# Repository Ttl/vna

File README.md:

Homemade 30 MHZ - 6 GHz single receiver VNA design files.

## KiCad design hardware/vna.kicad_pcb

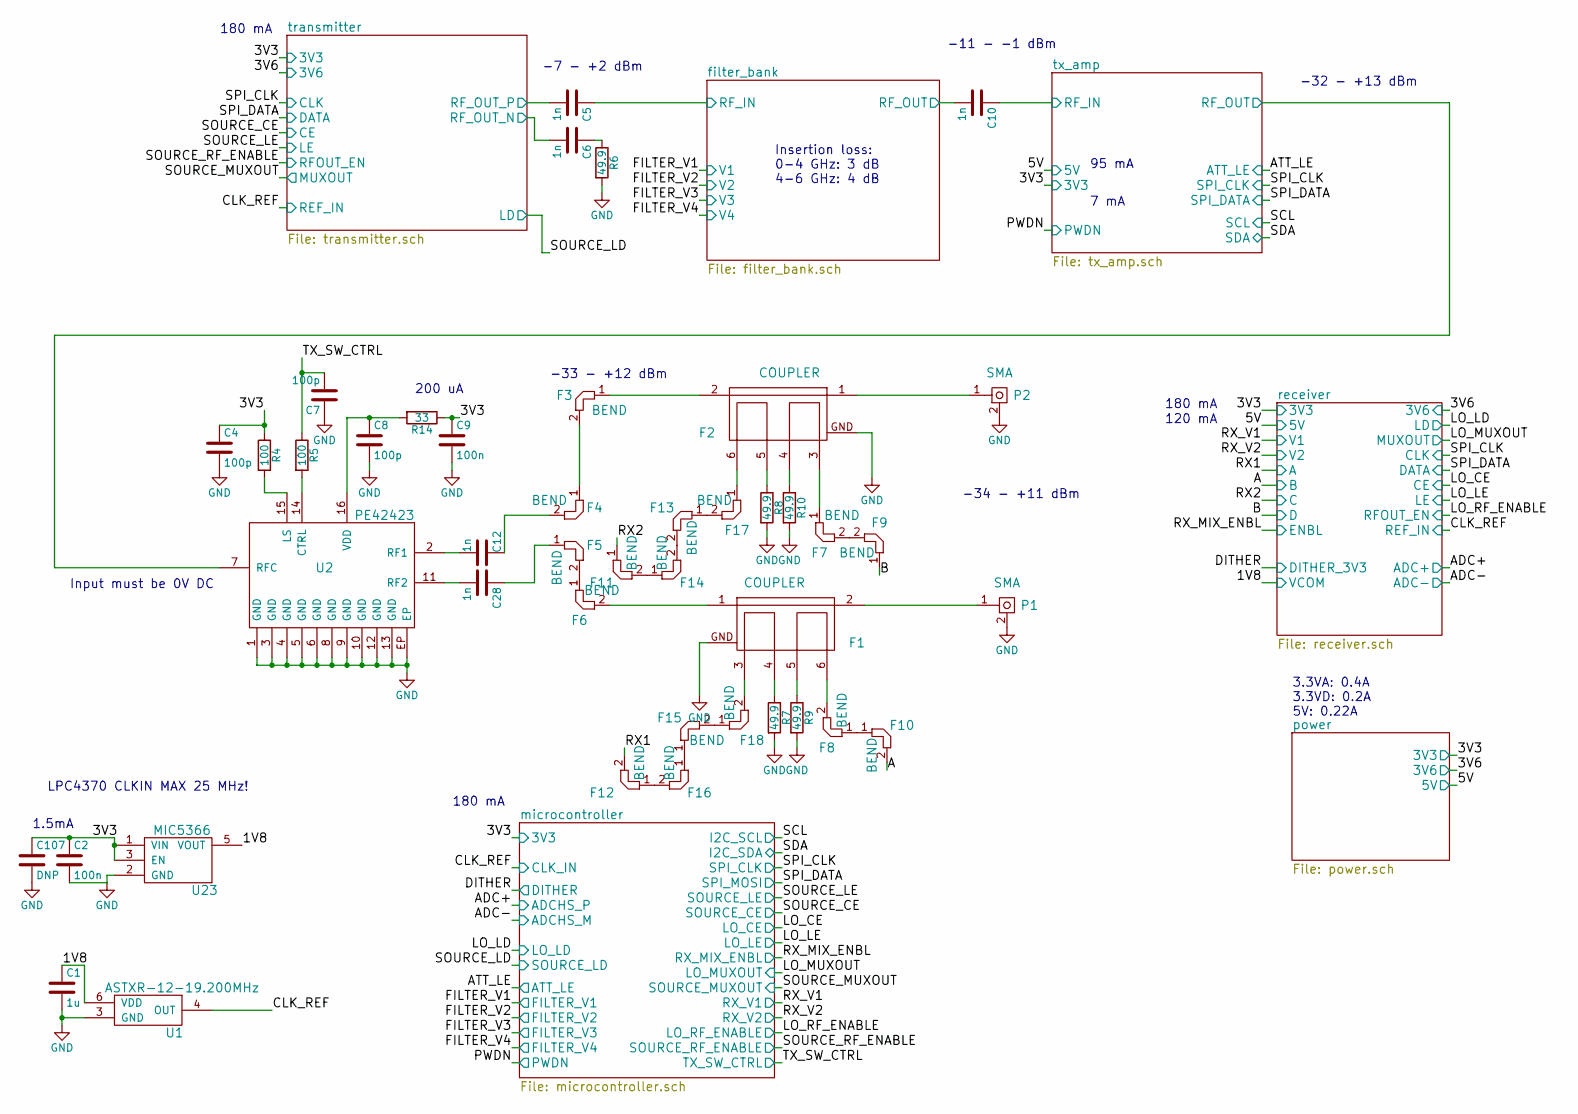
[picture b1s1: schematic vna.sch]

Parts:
C1: 1u; C_0402b
C2, C9: 100n; C_0402b
C4, C7, C8: 100p; C_0402b
C5, C6, C10, C12, C28: 1n; C_0402b
C107: DNP; C_0805b
F1, F2: COUPLER; coupler4
F3, F4, F5, F6, F7, F8, F9, F10, F11, F12, F13, F14, F15, F16, F17, F18: BEND; uwmiter_0.34_0.17_45
P1, P2: SMA; CONSMA003.062
R4, R5: 100; R_0402b
R6, R7, R8, R9, R10: 49.9; R_0402b
R14: 33; R_0402b
U1: ASTXR-12-19.200MHz; ASTRX-12
U2: PE42423; VQFN-16
U23: MIC5366; SOT-353

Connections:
/filter_bank/RF_IN: C5.1; also elsewhere on the board
/filter_bank/RF_OUT: C10.2; also elsewhere on the board
/microcontroller/3V3: C2.1, C4.1, C9.1, C107.1, R4.1, R14.1, U23.1 (VIN), U23.3 (EN); also elsewhere on the board
/microcontroller/CLK_IN: U1.4 (OUT); also elsewhere on the board
/microcontroller/TX_SW_CTRL: C7.2, R5.1; also elsewhere on the board
/receiver/A: F12.2; also elsewhere on the board
/receiver/B: F10.2; also elsewhere on the board
/receiver/C: F11.1; also elsewhere on the board
/receiver/D: F9.1; also elsewhere on the board
/receiver/VCOM: C1.1, U1.6 (VDD), U23.5 (VOUT); also elsewhere on the board
/transmitter/RF_OUT_N: C6.2; also elsewhere on the board
/transmitter/RF_OUT_P: C5.2; also elsewhere on the board
/tx_amp/RF_IN: C10.1; also elsewhere on the board
/tx_amp/RF_OUT: U2.7 (RFC); also elsewhere on the board
GND: C1.2, C2.2, C4.2, C7.1, C8.2, C9.2, C107.2, F1.GND, F2.GND, P1.2, P2.2, R6.2, R7.2, R8.2, R9.2, R10.2, U1.3 (GND), U2.1 (GND), U2.3 (GND), U2.4 (GND), U2.5 (GND), U2.6 (GND), U2.8 (GND), U2.9 (GND), U2.10 (GND), U2.12 (GND), U2.13 (GND), U2.EP, U23.2 (GND); also elsewhere on the board
unnamed: C6.1, R6.1
unnamed: C8.1, R14.2, U2.16 (VDD)
unnamed: C12.1, F4.2
unnamed: C12.2, U2.2 (RF1)
unnamed: C28.1, F5.1
unnamed: C28.2, U2.11 (RF2)
unnamed: F1.1, F6.2
unnamed: F1.2, P1.1
unnamed: F1.3, F18.2
unnamed: F1.4, R7.1
unnamed: F1.5, R9.1
unnamed: F1.6, F8.2
unnamed: F2.1, P2.1
unnamed: F2.2, F3.1
unnamed: F2.3, F7.1
unnamed: F2.4, R10.1
unnamed: F2.5, R8.1
unnamed: F3.2, F4.1
unnamed: F5.2, F6.1
unnamed: F7.2, F9.2
unnamed: F8.1, F10.1
unnamed: F11.2, F14.1
unnamed: F12.1, F16.2
unnamed: F13.1, F17.2
unnamed: F13.2, F14.2
unnamed: F15.1, F16.1
unnamed: F15.2, F18.1
unnamed: F2.6, F17.1
unnamed: R4.2, U2.15 (LS)
unnamed: R5.2, U2.14 (CTRL)

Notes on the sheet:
1.5mA
Input must be 0V DC
Insertion loss: 0-4 GHz: 3 dB 4-6 GHz: 4 dB
-7 - +2 dBm
-11 - -1 dBm
-32 - +13 dBm
-33 - +12 dBm
-34 - +11 dBm
200 uA
180 mA
120 mA
3.3VA: 0.4A 3.3VD: 0.2A 5V: 0.22A
LPC4370 CLKIN MAX 25 MHz!
95 mA
7 mA

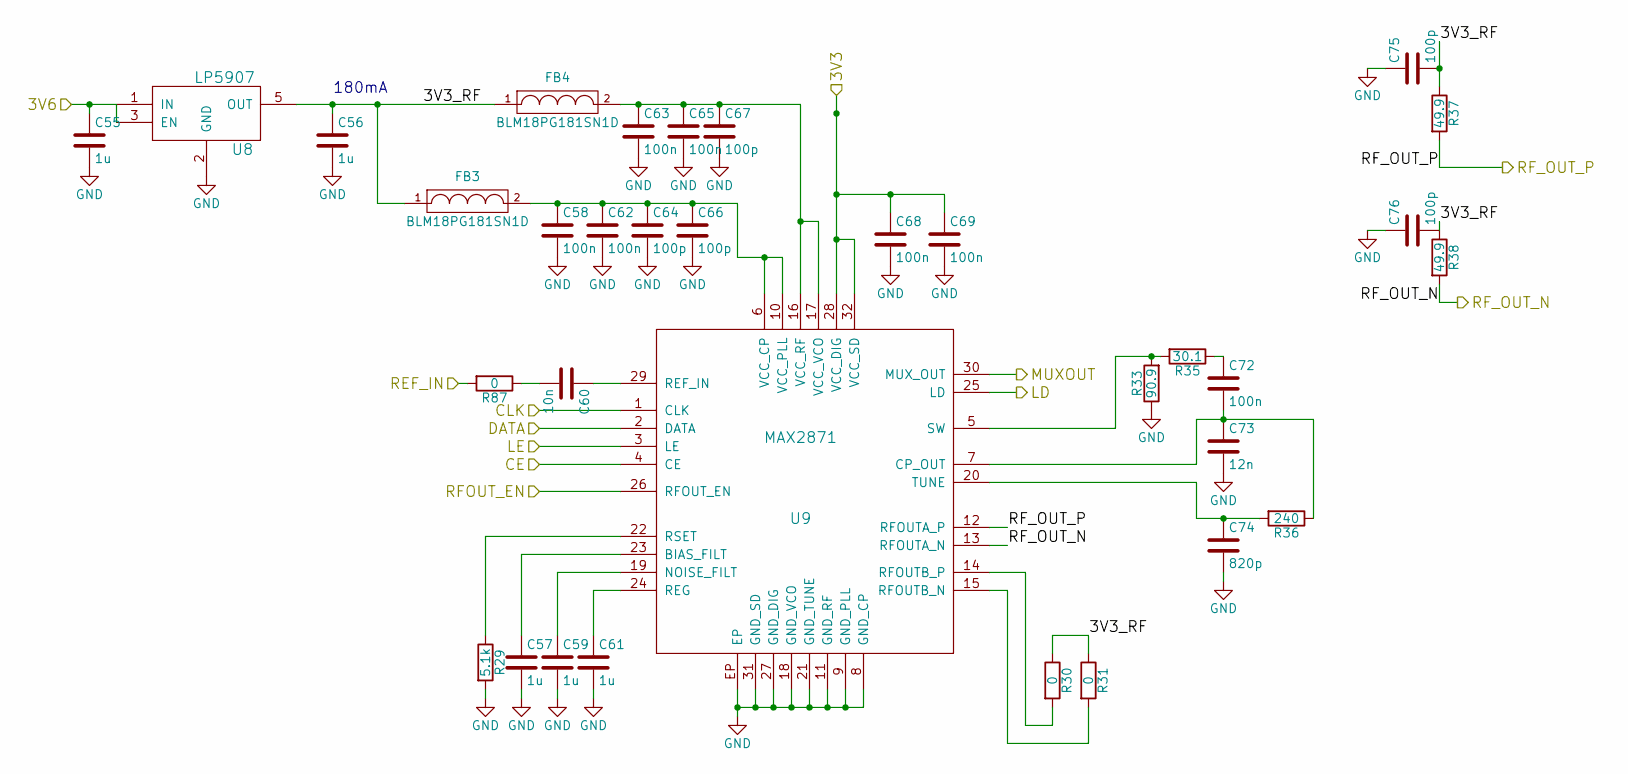
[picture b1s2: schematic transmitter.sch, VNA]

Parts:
C13, C14, C15, C17, C19: 1u; C_0603b
C16, C20, C21, C23, C26, C27, C30: 100n; C_0402b
C18: 10n; C_0402b
C22, C24, C25, C33, C34: 100p; C_0402b
C31: 12n; C_0402b
C32: 820p; C_0402b
FB1, FB2: BLM18PG181SN1D; C_0603b
R11: 5.1k; R_0402b
R12, R13, R86: 0; R_0402b
R15: 90.9; R_0402b
R17: 30.1; R_0402b
R18: 240; R_0402b
R19, R20: 49.9; R_0402b
U4: LP5907; SOT-23-5
U5: MAX2871; TQFN-32

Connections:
/microcontroller/3V3: C26.1, C27.1, U5.28 (VCC_DIG), U5.32 (VCC_SD); also elsewhere on the board
/microcontroller/CLK_IN: R86.2; also elsewhere on the board
/power/3V6: C13.1, U4.1 (IN), U4.3 (EN); also elsewhere on the board
/receiver/CLK: U5.1 (CLK); also elsewhere on the board
/receiver/DATA: U5.2 (DATA); also elsewhere on the board
/transmitter/3V3_RF: C14.1, C33.2, C34.2, FB1.1, FB2.1, R12.1, R13.1, R19.1, R20.1, U4.5 (OUT)
/transmitter/CE: U5.4 (CE); also elsewhere on the board
/transmitter/LD: U5.25 (LD); also elsewhere on the board
/transmitter/LE: U5.3 (LE); also elsewhere on the board
/transmitter/MUXOUT: U5.30 (MUX_OUT); also elsewhere on the board
/transmitter/RFOUT_EN: U5.26 (RFOUT_EN); also elsewhere on the board
/transmitter/RF_OUT_N: R20.2, U5.13 (RFOUTA_N); also elsewhere on the board
/transmitter/RF_OUT_P: R19.2, U5.12 (RFOUTA_P); also elsewhere on the board
GND: C13.2, C14.2, C15.2, C16.2, C17.2, C19.2, C20.2, C21.2, C22.2, C23.2, C24.2, C25.2, C26.2, C27.2, C31.2, C32.2, C33.1, C34.1, R11.2, R15.1, U4.2 (GND), U5.8 (GND_CP), U5.9 (GND_PLL), U5.11 (GND_RF), U5.18 (GND_VCO), U5.21 (GND_TUNE), U5.27 (GND_DIG), U5.31 (GND_SD), U5.EP; also elsewhere on the board
unnamed: C15.1, U5.23 (BIAS_FILT)
unnamed: C16.1, C20.1, C22.1, C24.1, FB1.2, U5.6 (VCC_CP), U5.10 (VCC_PLL)
unnamed: C17.1, U5.19 (NOISE_FILT)
unnamed: C18.1, U5.29 (REF_IN)
unnamed: C18.2, R86.1
unnamed: C19.1, U5.24 (REG)
unnamed: C21.1, C23.1, C25.1, FB2.2, U5.16 (VCC_RF), U5.17 (VCC_VCO)
unnamed: C30.1, R17.1
unnamed: C30.2, C31.1, R18.1, U5.7 (CP_OUT)
unnamed: C32.1, R18.2, U5.20 (TUNE)
unnamed: R11.1, U5.22 (RSET)
unnamed: R12.2, U5.14 (RFOUTB_P)
unnamed: R13.2, U5.15 (RFOUTB_N)
unnamed: R15.2, R17.2, U5.5 (SW)

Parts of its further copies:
C55, C56, C57, C59, C61: 1u; C_0603b
C58, C62, C63, C65, C68, C69, C72: 100n; C_0402b
C60: 10n; C_0402b
C64, C66, C67, C75, C76: 100p; C_0402b
C73: 12n; C_0402b
C74: 820p; C_0402b
FB3, FB4: BLM18PG181SN1D; C_0603b
R29: 5.1k; R_0402b
R30, R31, R87: 0; R_0402b
R33: 90.9; R_0402b
R35: 30.1; R_0402b
R36: 240; R_0402b
R37, R38: 49.9; R_0402b
U8: LP5907; SOT-23-5
U9: MAX2871; TQFN-32

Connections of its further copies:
/microcontroller/3V3: C68.1, C69.1, U9.28 (VCC_DIG), U9.32 (VCC_SD); also elsewhere on the board
/microcontroller/CLK_IN: R87.2; also elsewhere on the board
/microcontroller/LO_MUXOUT: U9.30 (MUX_OUT); also elsewhere on the board
/microcontroller/LO_RF_ENABLE: U9.26 (RFOUT_EN); also elsewhere on the board
/power/3V6: C55.1, U8.1 (IN), U8.3 (EN); also elsewhere on the board
/receiver/CE: U9.4 (CE); also elsewhere on the board
/receiver/CLK: U9.1 (CLK); also elsewhere on the board
/receiver/DATA: U9.2 (DATA); also elsewhere on the board
/receiver/LD: U9.25 (LD); also elsewhere on the board
/receiver/LE: U9.3 (LE); also elsewhere on the board
/receiver/lo_synth/3V3_RF: C56.1, C75.2, C76.2, FB3.1, FB4.1, R30.1, R31.1, R37.1, R38.1, U8.5 (OUT)
/receiver/lo_synth/RF_OUT_N: R38.2, U9.13 (RFOUTA_N); also elsewhere on the board
/receiver/lo_synth/RF_OUT_P: R37.2, U9.12 (RFOUTA_P); also elsewhere on the board
GND: C55.2, C56.2, C57.2, C58.2, C59.2, C61.2, C62.2, C63.2, C64.2, C65.2, C66.2, C67.2, C68.2, C69.2, C73.2, C74.2, C75.1, C76.1, R29.2, R33.1, U8.2 (GND), U9.8 (GND_CP), U9.9 (GND_PLL), U9.11 (GND_RF), U9.18 (GND_VCO), U9.21 (GND_TUNE), U9.27 (GND_DIG), U9.31 (GND_SD), U9.EP; also elsewhere on the board
unnamed: C57.1, U9.23 (BIAS_FILT)
unnamed: C58.1, C62.1, C64.1, C66.1, FB3.2, U9.6 (VCC_CP), U9.10 (VCC_PLL)
unnamed: C59.1, U9.19 (NOISE_FILT)
unnamed: C60.1, U9.29 (REF_IN)
unnamed: C60.2, R87.1
unnamed: C61.1, U9.24 (REG)
unnamed: C63.1, C65.1, C67.1, FB4.2, U9.16 (VCC_RF), U9.17 (VCC_VCO)
unnamed: C72.1, R35.1
unnamed: C72.2, C73.1, R36.1, U9.7 (CP_OUT)
unnamed: C74.1, R36.2, U9.20 (TUNE)
unnamed: R29.1, U9.22 (RSET)
unnamed: R30.2, U9.14 (RFOUTB_P)
unnamed: R31.2, U9.15 (RFOUTB_N)
unnamed: R33.2, R35.2, U9.5 (SW)

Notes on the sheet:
180mA

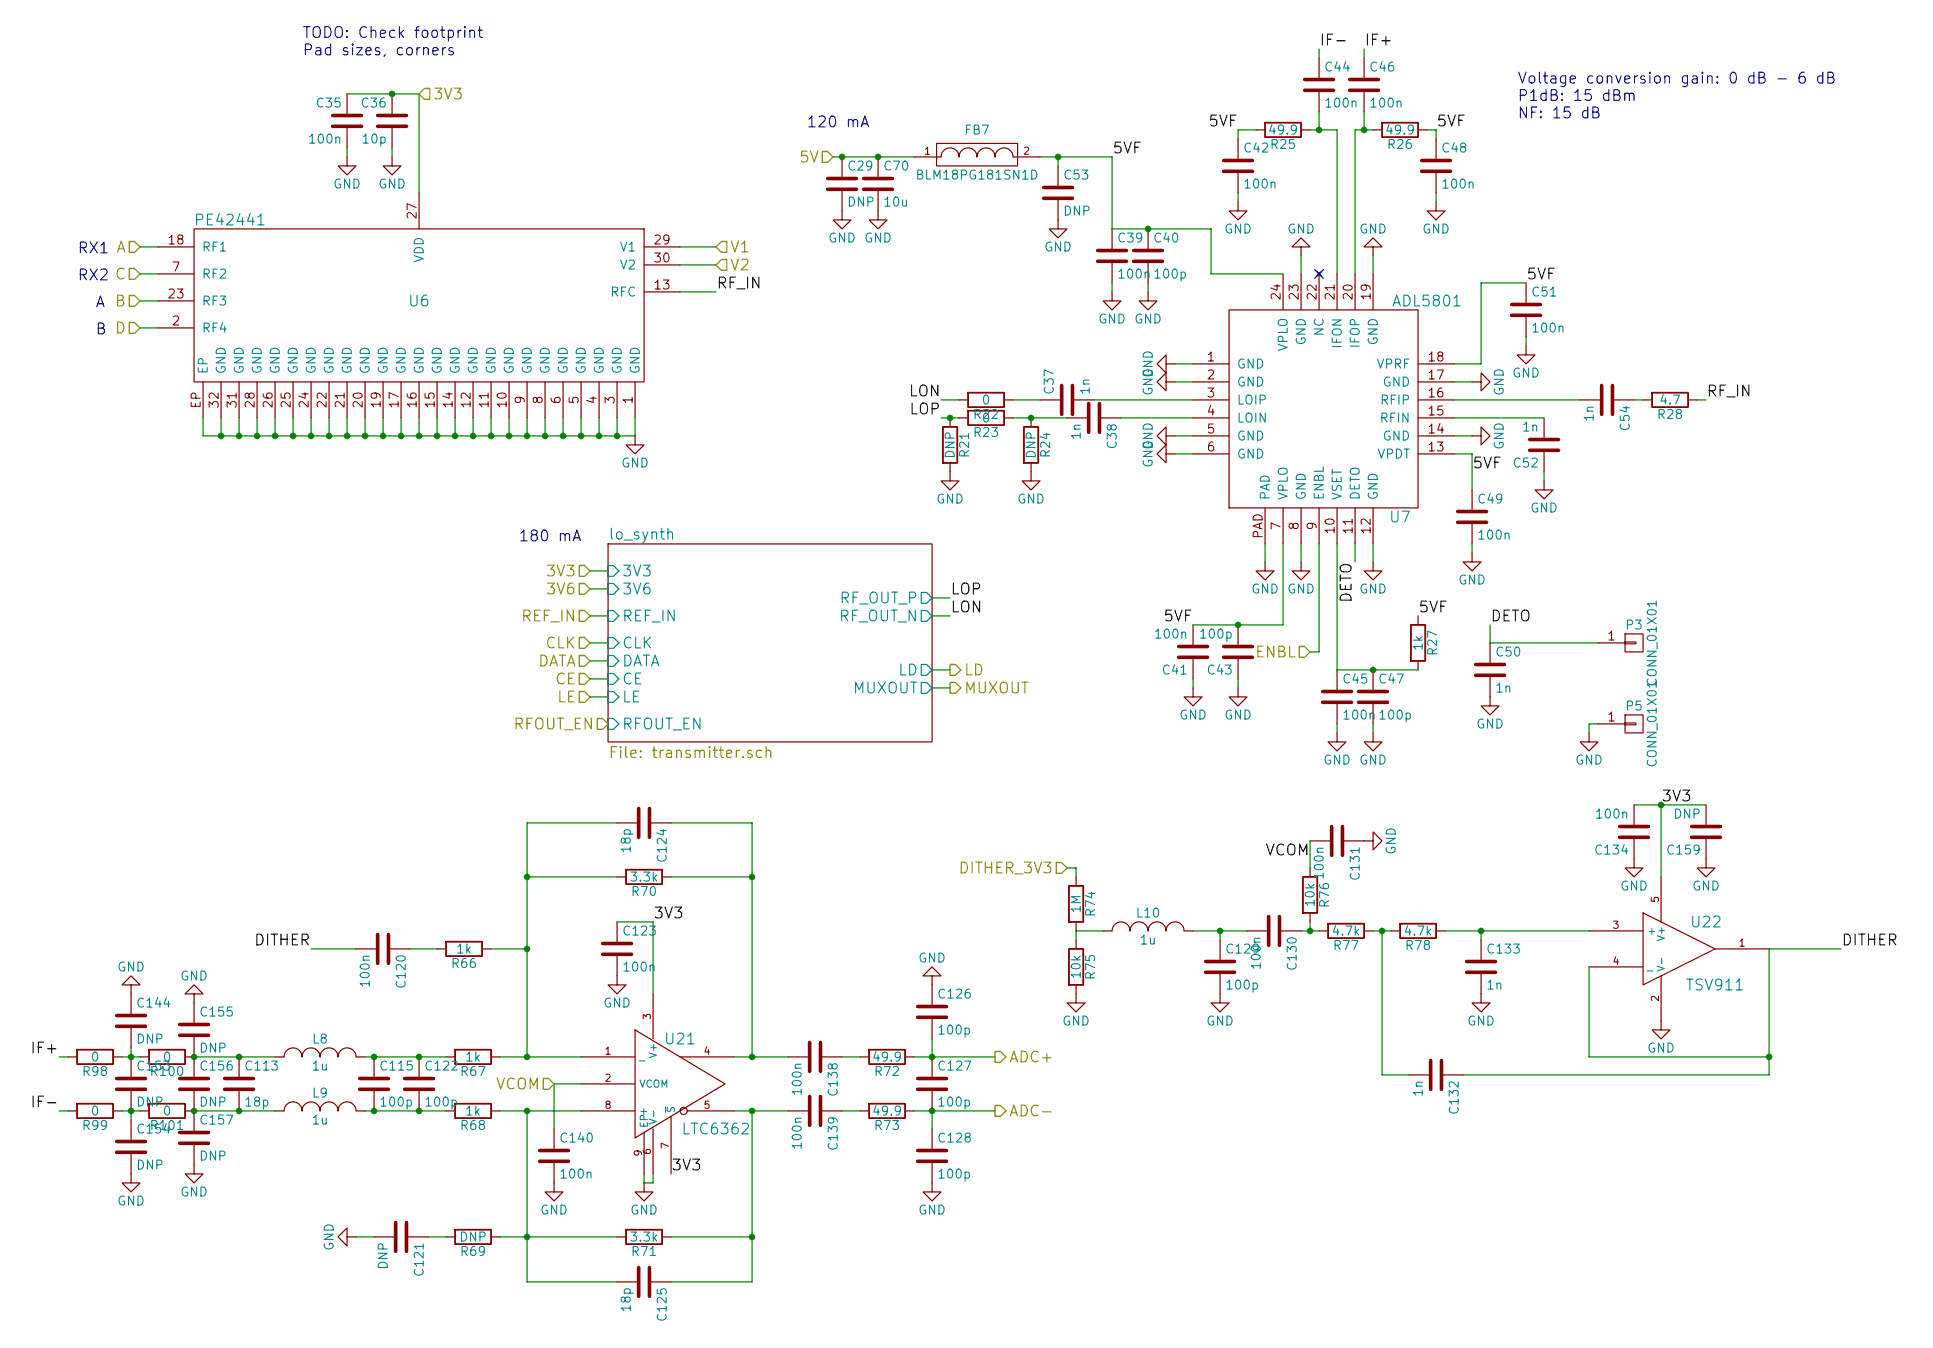
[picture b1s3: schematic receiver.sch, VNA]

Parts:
C29: DNP; C_0603b
C35, C39, C41, C42, C44, C45, C46, C48, C49, C51, C120, C123, C130, C131, C134, C138, C139, C140: 100n; C_0402b
C36: 10p; C_0402b
C37, C38, C50, C52, C54, C132, C133: 1n; C_0402b
C40, C43, C47, C115, C122, C126, C127, C128, C129: 100p; C_0402b
C53, C159: DNP; C_0805b
C70: 10u; C_0805b
C113, C124, C125: 18p; C_0402b
C121, C144, C153, C154, C155, C156, C157: DNP; C_0402b
FB7: BLM18PG181SN1D; C_0603b
L8, L9, L10: 1u; C_0603b
P3, P5: CONN_01X01; TP_1.00
R21, R24, R69: DNP; R_0402b
R22, R23, R98, R99, R100, R101: 0; R_0402b
R25, R26, R72, R73: 49.9; R_0402b
R27, R66, R67, R68: 1k; R_0402b
R28: 4.7; R_0402b
R70, R71: 3.3k; R_0402b
R74: 1M; R_0402b
R75, R76: 10k; R_0402b
R77, R78: 4.7k; R_0402b
U6: PE42441; VFQFN-32
U7: ADL5801; VFQFN-24
U21: LTC6362; DFN-8-1EP_3x3mm_Pitch0.5mm
U22: TSV911; SOT-23-5

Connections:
/microcontroller/3V3: C35.1, C36.1, C123.1, C134.2, C159.2, U6.27 (VDD), U21.3 (V+), U21.7 (~S), U22.5 (V+); also elsewhere on the board
/microcontroller/DITHER: R74.1; also elsewhere on the board
/microcontroller/RX_V1: U6.29 (V1); also elsewhere on the board
/microcontroller/RX_V2: U6.30 (V2); also elsewhere on the board
/power/5V: C29.1, C70.1, FB7.1; also elsewhere on the board
/receiver/5VF: C39.1, C40.1, C41.2, C42.1, C43.2, C48.1, C49.1, C51.1, C53.1, FB7.2, R25.2, R26.1, R27.1, U7.7 (VPLO), U7.13 (VPDT), U7.18 (VPRF), U7.24 (VPLO)
/receiver/A: U6.18 (RF1); also elsewhere on the board
/receiver/ADC+: C126.2, C127.1, R72.1; also elsewhere on the board
/receiver/ADC-: C127.2, C128.1, R73.1; also elsewhere on the board
/receiver/B: U6.23 (RF3); also elsewhere on the board
/receiver/C: U6.7 (RF2); also elsewhere on the board
/receiver/D: U6.2 (RF4); also elsewhere on the board
/receiver/DETO: C50.1, P3.1, U7.11 (DETO)
/receiver/DITHER: C120.2, C132.1, U22.1, U22.4 (_)
/receiver/ENBL: U7.9 (ENBL); also elsewhere on the board
/receiver/IF+: C46.1, R98.2
/receiver/IF-: C44.1, R99.2
/receiver/RF_IN: R28.1, U6.13 (RFC)
/receiver/VCOM: C131.2, C140.1, R76.1, U21.2 (VCOM); also elsewhere on the board
/receiver/lo_synth/RF_OUT_N: R22.2; also elsewhere on the board
/receiver/lo_synth/RF_OUT_P: R21.1, R23.2; also elsewhere on the board
GND: C29.2, C35.2, C36.2, C39.2, C40.2, C41.1, C42.2, C43.1, C45.2, C47.2, C48.2, C49.2, C50.2, C51.2, C52.1, C53.2, C70.2, C121.2, C123.2, C126.1, C128.2, C129.2, C131.1, C133.2, C134.1, C140.2, C144.1, C154.2, C155.1, C157.2, C159.1, P5.1, R21.2, R24.2, R75.2, U6.1 (GND), U6.3 (GND), U6.4 (GND), U6.5 (GND), U6.6 (GND), U6.8 (GND), U6.9 (GND), U6.10 (GND), U6.11 (GND), U6.12 (GND), U6.14 (GND), U6.15 (GND), U6.16 (GND), U6.17 (GND), U6.19 (GND), U6.20 (GND), U6.21 (GND), U6.22 (GND), U6.24 (GND), U6.25 (GND), U6.26 (GND), U6.28 (GND), U6.31 (GND), U6.32 (GND), U6.EP, U7.1 (GND), U7.2 (GND), U7.5 (GND), U7.6 (GND), U7.8 (GND), U7.12 (GND), U7.14 (GND), U7.17 (GND), U7.19 (GND), U7.23 (GND), U7.PAD, U21.6 (V-), U21.9 (EP), U22.2 (V-); also elsewhere on the board
unnamed: C37.1, R22.1
unnamed: C37.2, U7.3 (LOIP)
unnamed: C38.1, U7.4 (LOIN)
unnamed: C38.2, R23.1, R24.1
unnamed: C44.2, R25.1, U7.21 (IFON)
unnamed: C45.1, C47.1, R27.2, U7.10 (VSET)
unnamed: C46.2, R26.2, U7.20 (IFOP)
unnamed: C52.2, U7.15 (RFIN)
unnamed: C54.1, R28.2
unnamed: C54.2, U7.16 (RFIP)
unnamed: C113.1, C155.2, C156.1, L8.1, R100.1
unnamed: C113.2, C156.2, C157.1, L9.1, R101.1
unnamed: C115.1, C122.1, L8.2, R67.2
unnamed: C115.2, C122.2, L9.2, R68.2
unnamed: C120.1, R66.2
unnamed: C121.1, R69.2
unnamed: C124.1, C138.2, R70.1, U21.4
unnamed: C124.2, R66.1, R67.1, R70.2, U21.1 (_)
unnamed: C125.1, C139.2, R71.1, U21.5
unnamed: C125.2, R68.1, R69.1, R71.2, U21.8 (+)
unnamed: C129.1, C130.2, L10.2
unnamed: C130.1, R76.2, R77.2
unnamed: C132.2, R77.1, R78.2
unnamed: C133.1, R78.1, U22.3 (+)
unnamed: C138.1, R72.2
unnamed: C139.1, R73.2
unnamed: C144.2, C153.1, R98.1, R100.2
unnamed: C153.2, C154.1, R99.1, R101.2
unnamed: L10.1, R74.2, R75.1

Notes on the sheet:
TODO: Check footprint Pad sizes, corners
Voltage conversion gain: 0 dB - 6 dB P1dB: 15 dBm NF: 15 dB
120 mA
180 mA
RX1
RX2

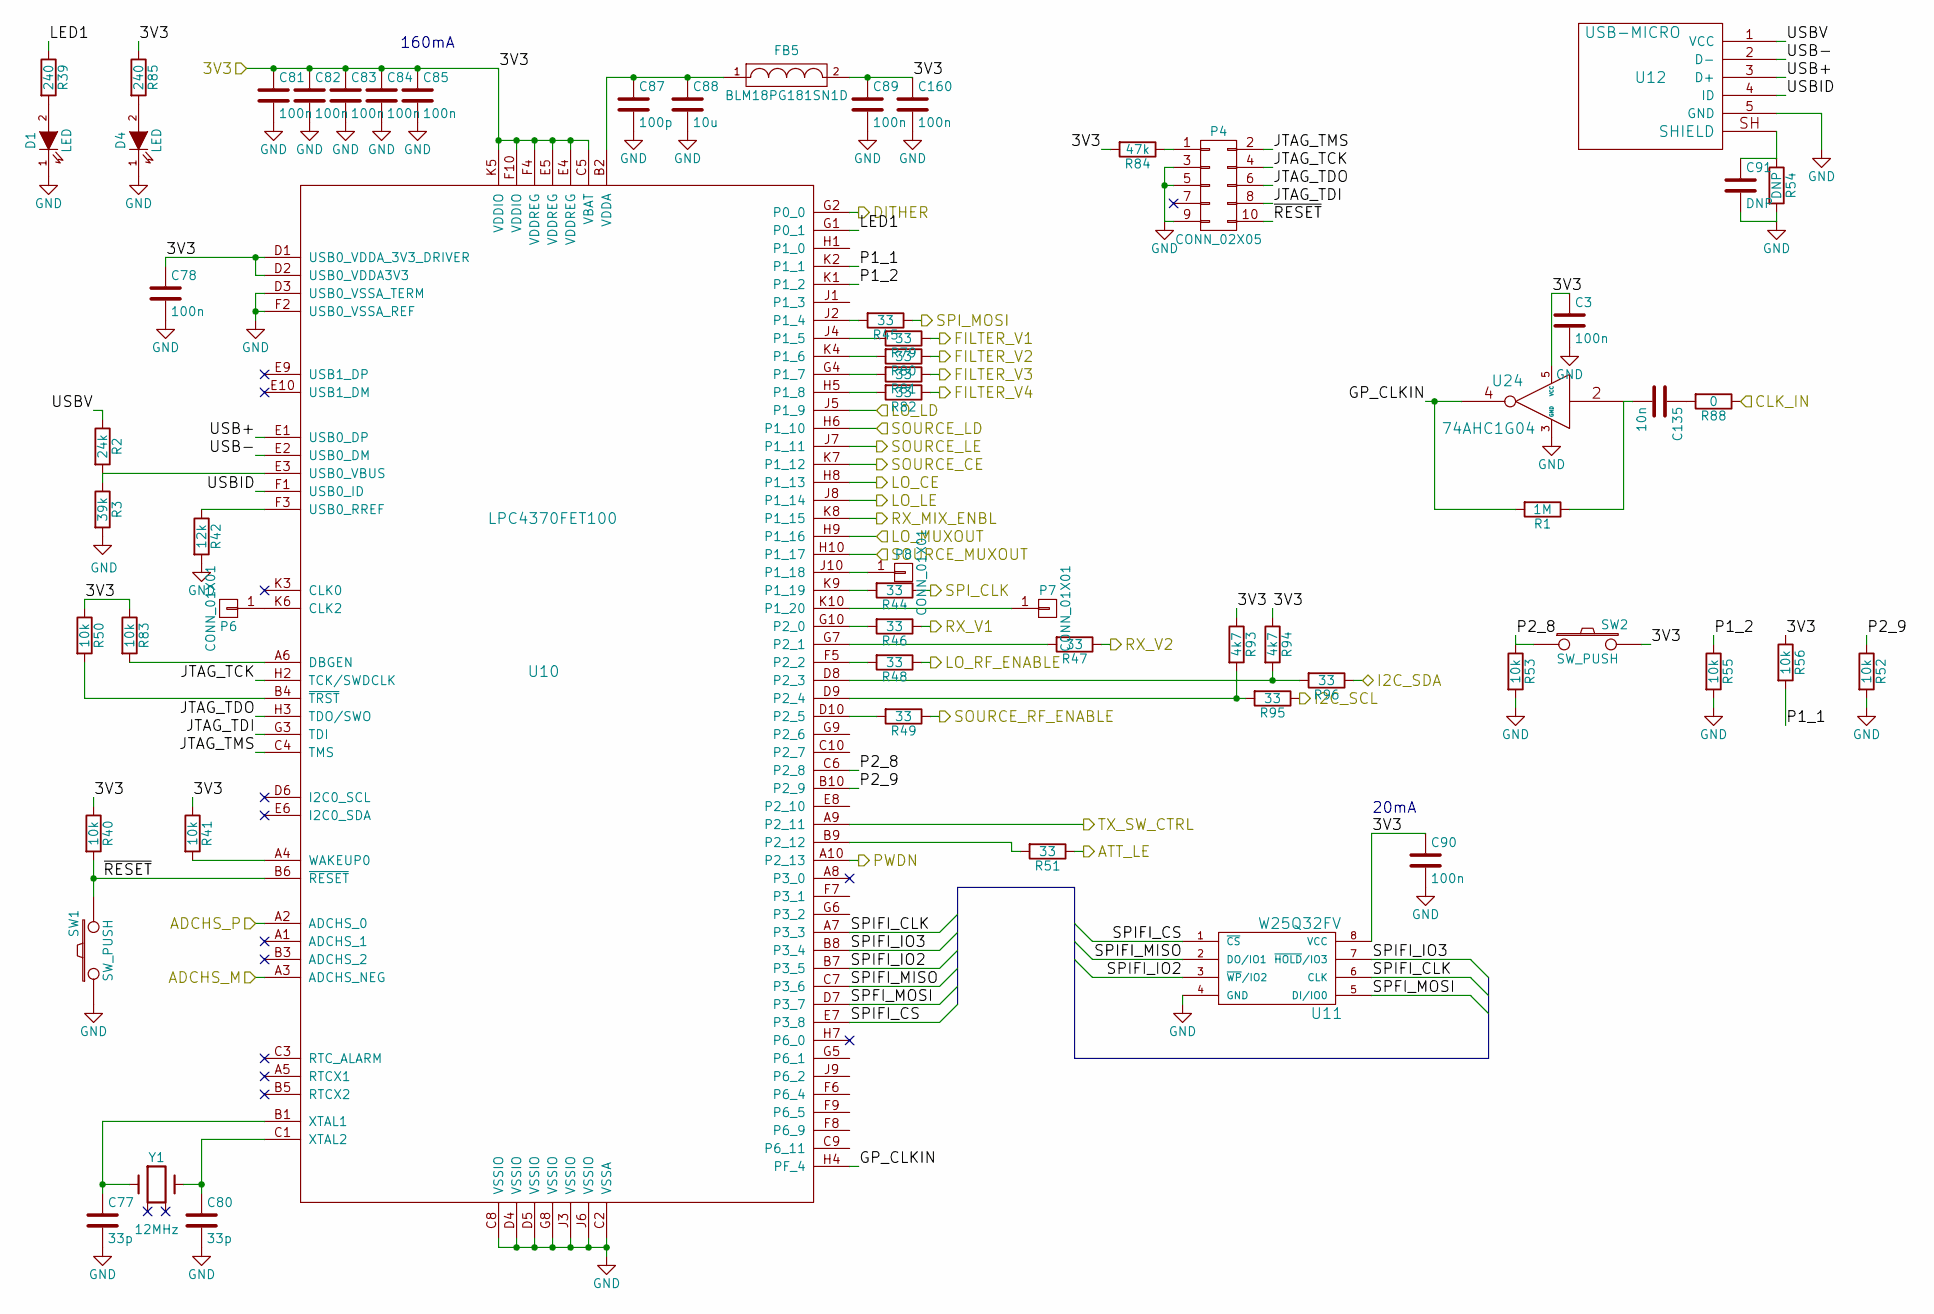
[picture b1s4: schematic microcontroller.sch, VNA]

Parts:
C3, C78, C81, C82, C83, C84, C85, C89, C90, C160: 100n; C_0402b
C77, C80: 33p; C_0402b
C87: 100p; C_0402b
C88: 10u; C_0805b
C91: DNP; C_0402b
C135: 10n; C_0402b
D1, D4: LED; LED_0603
FB5: BLM18PG181SN1D; C_0603b
P4: CONN_02X05; CNC-3220-10-0300-00
P6, P7, P8: CONN_01X01; TP_1.00
R1: 1M; R_0402b
R2: 24k; R_0402b
R3: 39k; R_0402b
R39, R85: 240; R_0402b
R40, R41, R50, R52, R53, R55, R56, R83: 10k; R_0402b
R42: 12k; R_0402b
R44, R45, R46, R47, R48, R49, R51, R79, R80, R81, R82, R95, R96: 33; R_0402b
R54: DNP; R_0402b
R84: 47k; R_0402b
R88: 0; R_0402b
R93, R94: 4k7; R_0402b
SW1, SW2: SW_PUSH; EVP-AWBA2A
U10: LPC4370FET100; TFBGA-100
U11: W25Q32FV; SOIJ-8_5.3x5.3mm_Pitch1.27mm
U12: USB-MICRO; USB_MICRO
U24: 74AHC1G04; SOT-353
Y1: 12MHz; XTAL_3.2x2.5

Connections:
/microcontroller/3V3: C3.1, C78.1, C81.1, C82.1, C83.1, C84.1, C85.1, C89.1, C90.1, C160.1, FB5.2, R40.1, R41.1, R50.1, R56.1, R83.1, R84.2, R85.1, R93.1, R94.1, SW2.2, U10.C5 (VBAT), U10.D1 (USB0_VDDA_3V3_DRIVER), U10.D2 (USB0_VDDA3V3), U10.E4 (VDDREG), U10.E5 (VDDREG), U10.F4 (VDDREG), U10.F10 (VDDIO), U10.K5 (VDDIO), U11.8 (VCC), U24.5 (VCC); also elsewhere on the board
/microcontroller/ATT_LE: R51.1; also elsewhere on the board
/microcontroller/CLK_IN: R88.1; also elsewhere on the board
/microcontroller/DITHER: U10.G2 (P0_0); also elsewhere on the board
/microcontroller/FILTER_V1: R79.1; also elsewhere on the board
/microcontroller/FILTER_V2: R80.1; also elsewhere on the board
/microcontroller/FILTER_V3: R81.1; also elsewhere on the board
/microcontroller/FILTER_V4: R82.1; also elsewhere on the board
/microcontroller/GP_CLKIN: R1.2, U10.H4 (PF_4), U24.4
/microcontroller/I2C_SCL: R95.1; also elsewhere on the board
/microcontroller/I2C_SDA: R96.1; also elsewhere on the board
/microcontroller/JTAG_TCK: P4.4, U10.H2 (TCK/SWDCLK)
/microcontroller/JTAG_TDI: P4.8, U10.G3 (TDI)
/microcontroller/JTAG_TDO: P4.6, U10.H3 (TDO/SWO)
/microcontroller/JTAG_TMS: P4.2, U10.C4 (TMS)
/microcontroller/LED1: R39.1, U10.G1 (P0_1)
/microcontroller/LO_MUXOUT: U10.H9 (P1_16); also elsewhere on the board
/microcontroller/LO_RF_ENABLE: R48.1; also elsewhere on the board
/microcontroller/P1_1: R56.2, U10.K2 (P1_1)
/microcontroller/P1_2: R55.1, U10.K1 (P1_2)
/microcontroller/P2_8: R53.1, SW2.1, U10.C6 (P2_8)
/microcontroller/P2_9: R52.1, U10.B10 (P2_9)
/microcontroller/PWDN: U10.A10 (P2_13); also elsewhere on the board
/microcontroller/RX_V1: R46.1; also elsewhere on the board
/microcontroller/RX_V2: R47.1; also elsewhere on the board
/microcontroller/SPFI_MOSI: U10.D7 (P3_7), U11.5 (DI/IO0)
/microcontroller/SPIFI_CLK: U10.A7 (P3_3), U11.6 (CLK)
/microcontroller/SPIFI_CS: U10.E7 (P3_8), U11.1 (~CS)
/microcontroller/SPIFI_IO2: U10.B7 (P3_5), U11.3 (~WP~/IO2)
/microcontroller/SPIFI_IO3: U10.B8 (P3_4), U11.7 (~HOLD~/IO3)
/microcontroller/SPIFI_MISO: U10.C7 (P3_6), U11.2 (DO/IO1)
/microcontroller/TX_SW_CTRL: U10.A9 (P2_11); also elsewhere on the board
/microcontroller/USB+: U10.E1 (USB0_DP), U12.3 (D+)
/microcontroller/USB-: U10.E2 (USB0_DM), U12.2 (D-)
/microcontroller/USBID: U10.F1 (USB0_ID), U12.4 (ID)
/microcontroller/USBV: R2.1, U12.1 (VCC)
/microcontroller/~RESET: P4.10, R40.2, SW1.2, U10.B6 (~RESET)
/receiver/ADC+: U10.A2 (ADCHS_0); also elsewhere on the board
/receiver/ADC-: U10.A3 (ADCHS_NEG); also elsewhere on the board
/receiver/CE: U10.H8 (P1_13); also elsewhere on the board
/receiver/CLK: R44.1; also elsewhere on the board
/receiver/DATA: R45.1; also elsewhere on the board
/receiver/ENBL: U10.K8 (P1_15); also elsewhere on the board
/receiver/LD: U10.J5 (P1_9); also elsewhere on the board
/receiver/LE: U10.J8 (P1_14); also elsewhere on the board
/transmitter/CE: U10.K7 (P1_12); also elsewhere on the board
/transmitter/LD: U10.H6 (P1_10); also elsewhere on the board
/transmitter/LE: U10.J7 (P1_11); also elsewhere on the board
/transmitter/MUXOUT: U10.H10 (P1_17); also elsewhere on the board
/transmitter/RFOUT_EN: R49.1; also elsewhere on the board
GND: C3.2, C77.2, C78.2, C80.2, C81.2, C82.2, C83.2, C84.2, C85.2, C87.2, C88.2, C89.2, C90.2, C91.2, C160.2, D1.1 (K), D4.1 (K), P4.3, P4.5, P4.9, R3.2, R42.2, R52.2, R53.2, R54.2, R55.2, SW1.1, U10.C2 (VSSA), U10.C8 (VSSIO), U10.D3 (USB0_VSSA_TERM), U10.D4 (VSSIO), U10.D5 (VSSIO), U10.F2 (USB0_VSSA_REF), U10.G8 (VSSIO), U10.J3 (VSSIO), U10.J6 (VSSIO), U11.4 (GND), U12.5 (GND), U24.3 (GND); also elsewhere on the board
unnamed: C77.1, U10.B1 (XTAL1), Y1.1
unnamed: C80.1, U10.C1 (XTAL2), Y1.3
unnamed: C87.1, C88.1, FB5.1, U10.B2 (VDDA)
unnamed: C91.1, R54.1, U12.SH (SHIELD)
unnamed: C135.1, R88.2
unnamed: C135.2, R1.1, U24.2
unnamed: D1.2 (A), R39.2
unnamed: D4.2 (A), R85.2
unnamed: P4.1, R84.1
unnamed: P6.1, U10.K6 (CLK2)
unnamed: P7.1, U10.K10 (P1_20)
unnamed: P8.1, U10.J10 (P1_18)
unnamed: R2.2, R3.1, U10.E3 (USB0_VBUS)
unnamed: R41.2, U10.A4 (WAKEUP0)
unnamed: R42.1, U10.F3 (USB0_RREF)
unnamed: R44.2, U10.K9 (P1_19)
unnamed: R45.2, U10.J2 (P1_4)
unnamed: R46.2, U10.G10 (P2_0)
unnamed: R47.2, U10.G7 (P2_1)
unnamed: R48.2, U10.F5 (P2_2)
unnamed: R49.2, U10.D10 (P2_5)
unnamed: R50.2, U10.B4 (~TRST)
unnamed: R51.2, U10.B9 (P2_12)
unnamed: R79.2, U10.J4 (P1_5)
unnamed: R80.2, U10.K4 (P1_6)
unnamed: R81.2, U10.G4 (P1_7)
unnamed: R82.2, U10.H5 (P1_8)
unnamed: R83.2, U10.A6 (DBGEN)
unnamed: R93.2, R95.2, U10.D9 (P2_4)
unnamed: R94.2, R96.2, U10.D8 (P2_3)

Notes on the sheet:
160mA
20mA

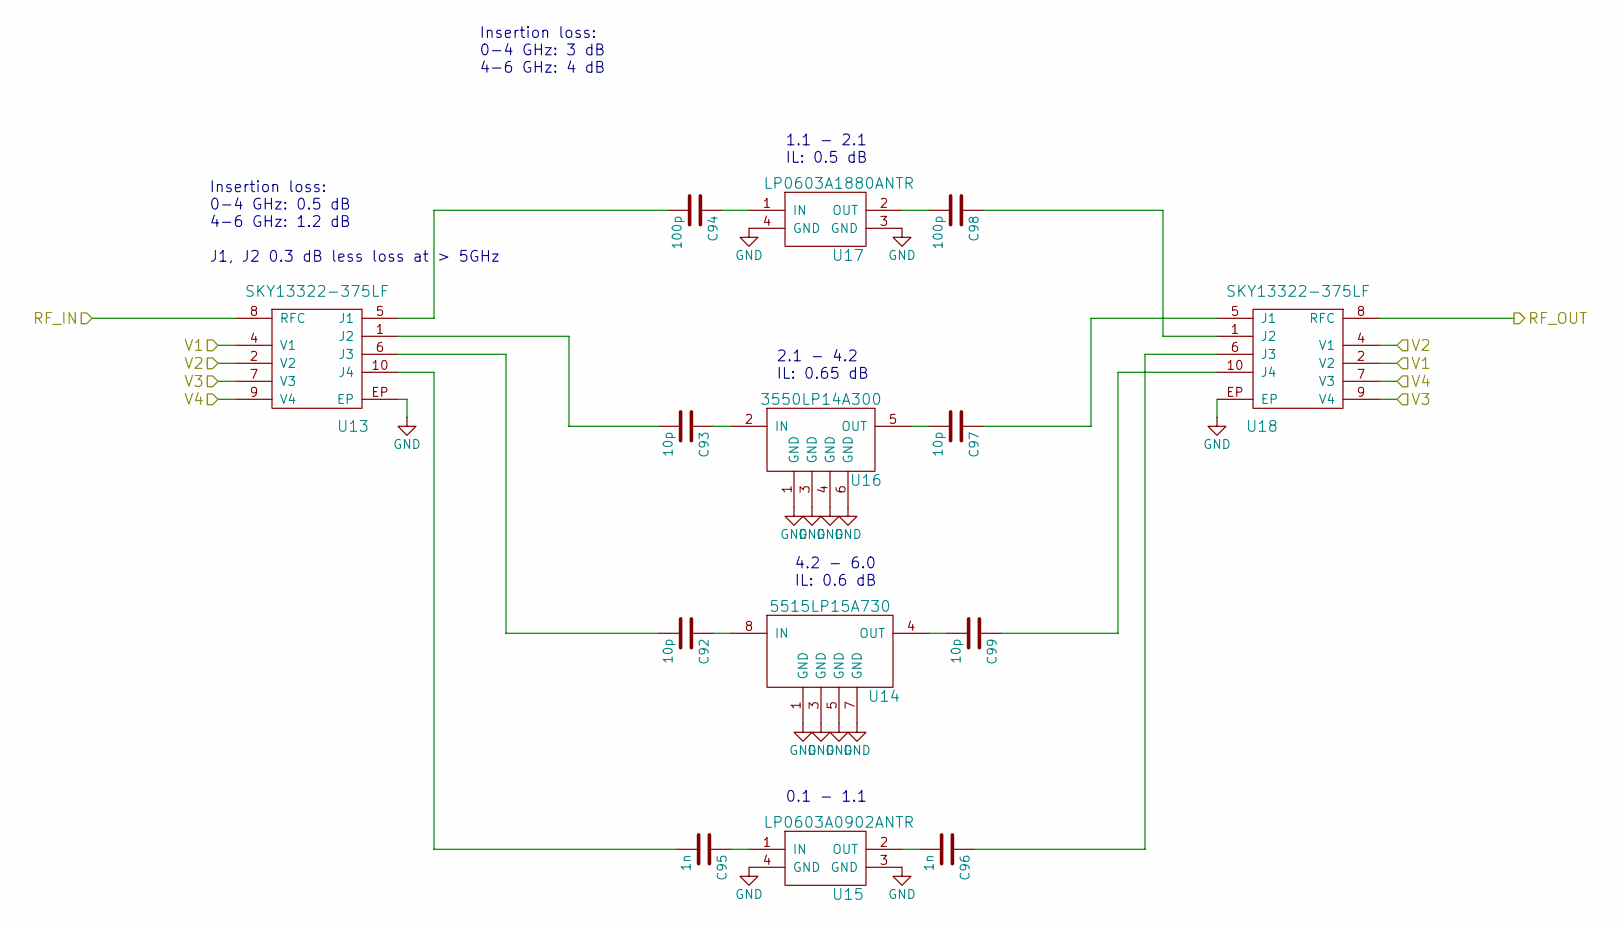
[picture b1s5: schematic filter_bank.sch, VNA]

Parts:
C92, C93, C97, C99: 10p; C_0402b
C94, C98: 100p; C_0402b
C95, C96: 1n; C_0402b
U13, U18: SKY13322-375LF; MLPD-10
U14: 5515LP15A730
U15: LP0603A0902ANTR; LP0603A0902
U16: 3550LP14A300
U17: LP0603A1880ANTR; LP0603A0902

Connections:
/filter_bank/RF_IN: U13.8 (RFC); also elsewhere on the board
/filter_bank/RF_OUT: U18.8 (RFC); also elsewhere on the board
/microcontroller/FILTER_V1: U13.4 (V1), U18.2 (V2); also elsewhere on the board
/microcontroller/FILTER_V2: U13.2 (V2), U18.4 (V1); also elsewhere on the board
/microcontroller/FILTER_V3: U13.7 (V3), U18.9 (V4); also elsewhere on the board
/microcontroller/FILTER_V4: U13.9 (V4), U18.7 (V3); also elsewhere on the board
GND: U13.EP, U14.1 (GND), U14.3 (GND), U14.5 (GND), U14.7 (GND), U15.3 (GND), U15.4 (GND), U16.1 (GND), U16.3 (GND), U16.4 (GND), U16.6 (GND), U17.3 (GND), U17.4 (GND), U18.EP; also elsewhere on the board
unnamed: C92.1, U14.8 (IN)
unnamed: C92.2, U13.6 (J3)
unnamed: C93.1, U16.2 (IN)
unnamed: C93.2, U13.1 (J2)
unnamed: C94.1, U17.1 (IN)
unnamed: C94.2, U13.5 (J1)
unnamed: C95.1, U15.1 (IN)
unnamed: C95.2, U13.10 (J4)
unnamed: C96.1, U18.6 (J3)
unnamed: C96.2, U15.2 (OUT)
unnamed: C97.1, U18.5 (J1)
unnamed: C97.2, U16.5 (OUT)
unnamed: C98.1, U18.1 (J2)
unnamed: C98.2, U17.2 (OUT)
unnamed: C99.1, U18.10 (J4)
unnamed: C99.2, U14.4 (OUT)

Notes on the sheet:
Insertion loss: 0-4 GHz: 0.5 dB 4-6 GHz: 1.2 dB J1, J2 0.3 dB less loss at > 5GHz
Insertion loss: 0-4 GHz: 3 dB 4-6 GHz: 4 dB
4.2 - 6.0 IL: 0.6 dB
2.1 - 4.2 IL: 0.65 dB
1.1 - 2.1 IL: 0.5 dB
0.1 - 1.1
